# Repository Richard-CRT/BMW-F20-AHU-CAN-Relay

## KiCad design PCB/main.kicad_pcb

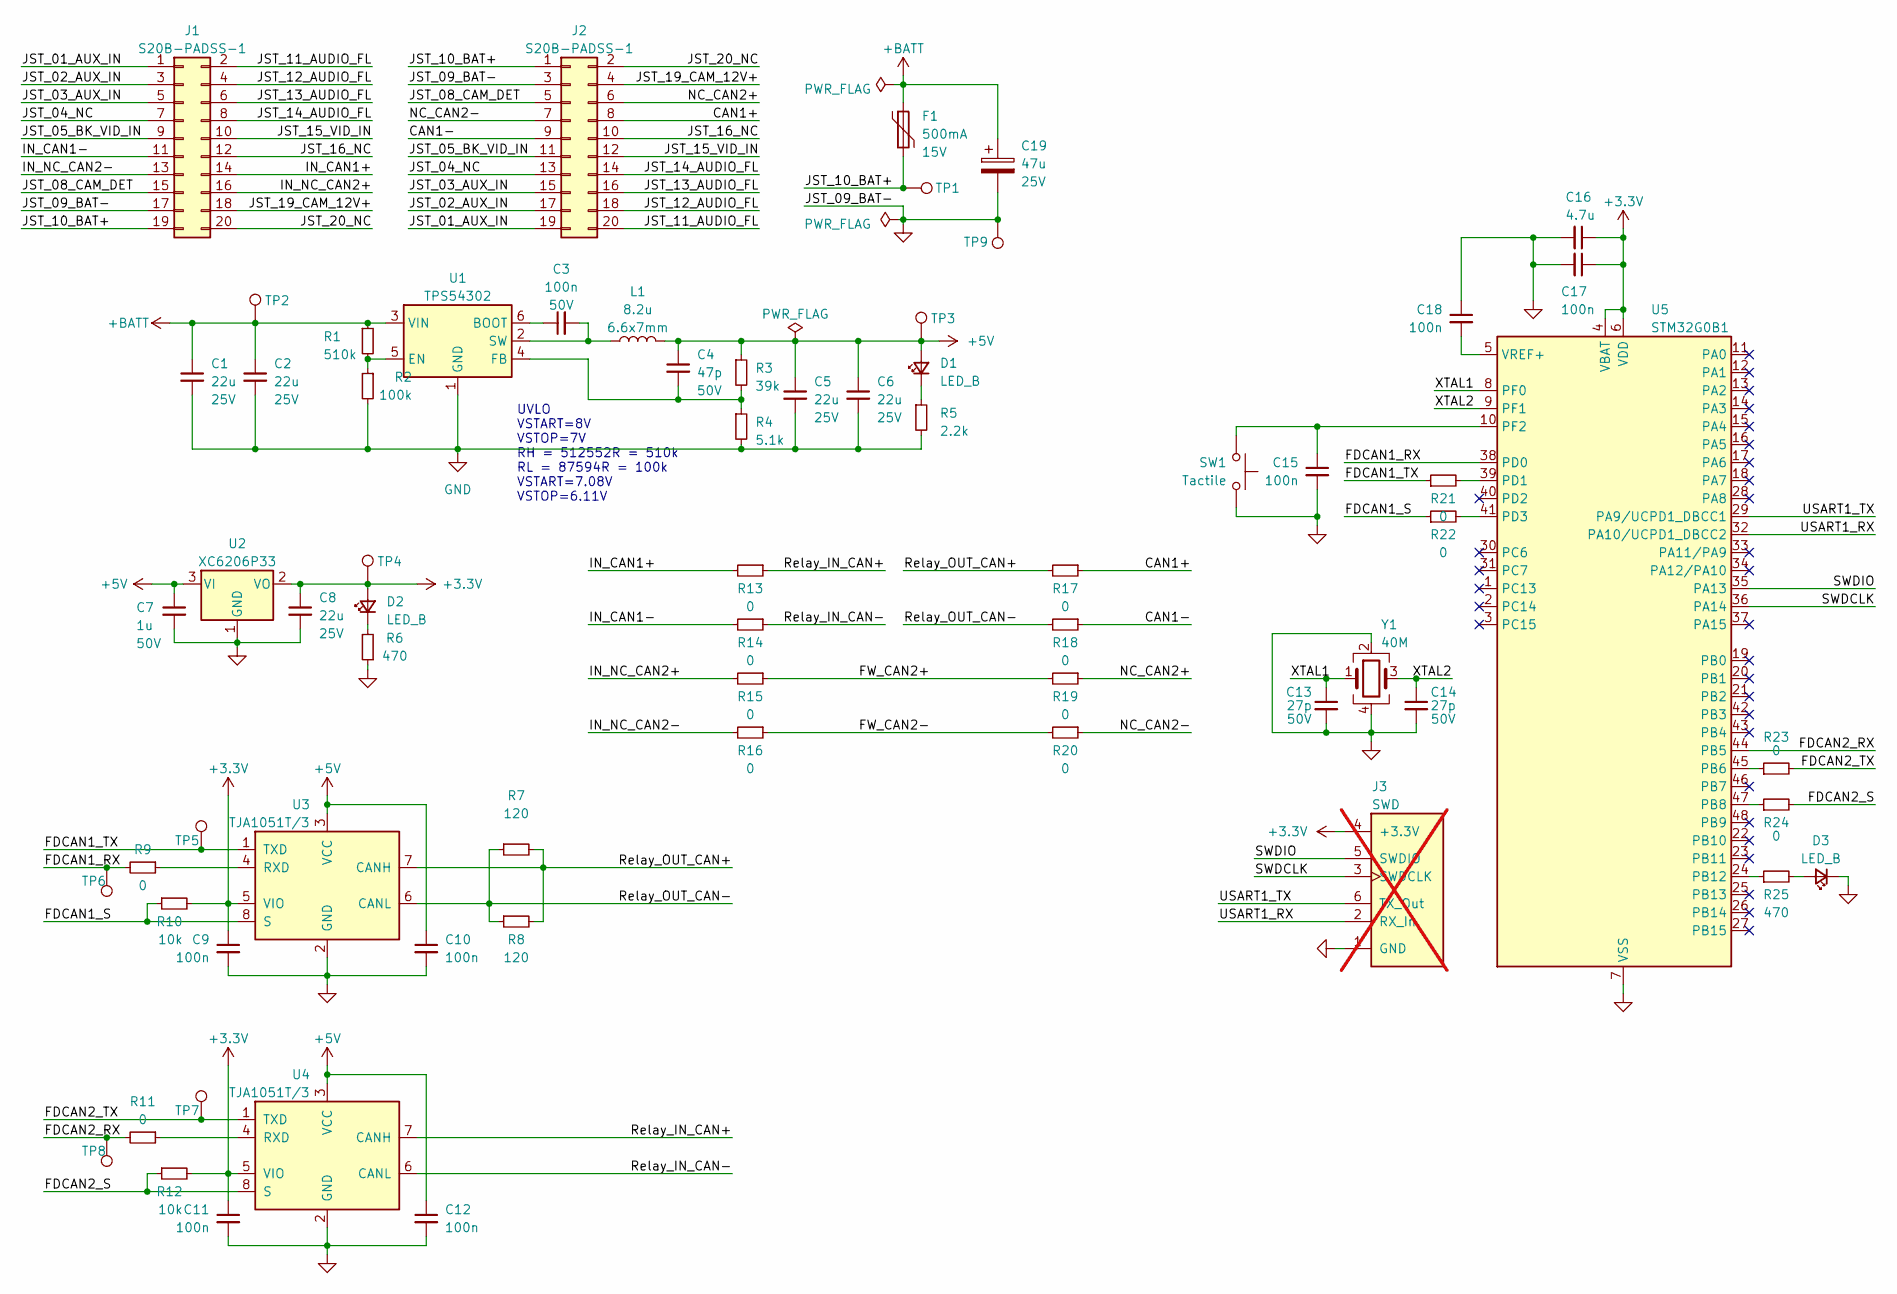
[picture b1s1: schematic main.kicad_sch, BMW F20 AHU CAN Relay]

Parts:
C1, C2, C5, C6, C8: 22u; C_1206_3216Metric; Capacitance Tolerance 10%; Voltage Rating 25V; MPN CL31A226KAHNNNE; LCSC C12891
C3, C9, C10, C11, C12, C15, C17, C18: 100n; C_0402_1005Metric; Capacitance Tolerance 10%; Voltage Rating 50V; MPN CL05B104KB54PNC; LCSC C307331
C4: 47p; C_0402_1005Metric; Capacitance Tolerance 5%; Voltage Rating 50V; MPN 0402CG470J500NT; LCSC C1567
C7: 1u; C_0805_2012Metric; Capacitance Tolerance 10%; Voltage Rating 50V; MPN CL21B105KBFNNNE; LCSC C28323
C13, C14: 27p; C_0402_1005Metric; Capacitance Tolerance 5%; Voltage Rating 50V; MPN 0402CG270J500NT; LCSC C1557
C16: 4.7u; C_0603_1608Metric; Capacitance Tolerance 10%; Voltage Rating 16V; MPN CL10A475KO8NNNC; LCSC C19666
C19: 47u; CP_Elec_6.3x5.8; Capacitance Tolerance 20%; Voltage Rating 25V; MPN EEE-FK1E470P; LCSC C178545
D1, D2, D3: LED_B; LED_0603_1608Metric; Forward Voltage 2.8V; MPN 19-217/BHC-ZL1M2RY/3T; LCSC C72041
F1: 500mA; CMP-0076; Max Voltage 15V; MPN 1812L050PR; LCSC C151169
J1, J2: S20B-PADSS-1; CMP-0012; MPN S20B-PADSS-1
J3: SWD; CMP-0053; not fitted
L1: 8.2u; CMP-0058; Inductance Tolerance 20%; MPN FXL0630-8R2-M; LCSC C167222
R1: 510k; R_0402_1005Metric; Tolerance 1%; Power Rating 62.5mW; MPN 0402WGF5103TCE; LCSC C11616
R2: 100k; R_0402_1005Metric; Tolerance 1%; Power Rating 62.5mW; MPN 0402WGF1003TCE; LCSC C25741
R3: 39k; R_0402_1005Metric; Tolerance 1%; Power Rating 62.5mW; MPN 0402WGF3902TCE; LCSC C25783
R4: 5.1k; R_0402_1005Metric; Tolerance 1%; Power Rating 62.5mW; MPN 0402WGF5101TCE; LCSC C25905
R5: 2.2k; R_0402_1005Metric; Tolerance 1%; Power Rating 62.5mW; MPN 0402WGF2201TCE; LCSC C25879
R6, R25: 470; R_0402_1005Metric; Tolerance 1%; Power Rating 62.5mW; MPN 0402WGF4700TCE; LCSC C25117
R7, R8: 120; R_1206_3216Metric; Tolerance 1%; Power Rating 250mW; MPN RC1206FR-07120RL; LCSC C114928
R9, R11, R13, R14, R15, R16, R17, R18, R19, R20, R21, R22, R23, R24: 0; R_0402_1005Metric; Tolerance 1%; Power Rating 62.5mW; MPN 0402WGF0000TCE; LCSC C17168
R10, R12: 10k; R_0402_1005Metric; Tolerance 1%; Power Rating 62.5mW; MPN 0402WGF1002TCE; LCSC C25744
SW1: Tactile; CMP-0072; MPN PTS810SJK250SMTRLFS; LCSC C221896
TP1, TP2, TP3, TP4, TP5, TP6, TP7, TP8, TP9: TestPoint; TestPoint_Pad_D1.0mm
U1: TPS54302; SOT-23-6; MPN TPS54302DDCR; LCSC C311983
U2: XC6206P33; CMP-0019; MPN XC6206P332MR-G; LCSC C5446
U3, U4: TJA1051T/3; SOIC-8_3.9x4.9mm_P1.27mm; MPN TJA1051T/3/1J; LCSC C38695
U5: STM32G0B1; LQFP-48_7x7mm_P0.5mm; MPN STM32G0B1CBT6; LCSC C2847904
Y1: 40M; Crystal_SMD_3225-4Pin_3.2x2.5mm; Tolerance 15 PPM; MPN X322540MPB4SI; LCSC C9010

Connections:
+3.3V: C8.1, C9.1, C11.1, C16.1, C17.1, D2.2 (A), J3.4 (+3.3V), R10.2, R12.2, TP4.1, U2.2 (VO), U3.5 (VIO), U4.5 (VIO), U5.4 (VBAT), U5.6 (VDD)
+5V: C4.1, C5.1, C6.1, C7.1, C10.1, C12.1, D1.2 (A), L1.2, R3.1, TP3.1, U2.3 (VI), U3.3 (VCC), U4.3 (VCC)
+BATT: C1.1, C2.1, C19.1, F1.1, R1.1, TP2.1, U1.3 (VIN)
/CAN1+: J2.8, R17.1
/CAN1-: J2.9, R18.1
/FDCAN1_RX: R9.2, TP6.1, U5.38 (PD0)
/FDCAN1_S: R10.1, R22.1, U3.8 (S)
/FDCAN1_TX: R21.1, TP5.1, U3.1 (TXD)
/FDCAN2_RX: R11.2, TP8.1, U5.44 (PB5)
/FDCAN2_S: R12.1, R24.2, U4.8 (S)
/FDCAN2_TX: R23.2, TP7.1, U4.1 (TXD)
/FW_CAN2+: R15.1, R19.2
/FW_CAN2-: R16.1, R20.2
/IN_CAN1+: J1.14, R13.2
/IN_CAN1-: J1.11, R14.2
/IN_NC_CAN2+: J1.16, R15.2
/IN_NC_CAN2-: J1.13, R16.2
/JST_01_AUX_IN: J1.1, J2.19
/JST_02_AUX_IN: J1.3, J2.17
/JST_03_AUX_IN: J1.5, J2.15
/JST_04_NC: J1.7, J2.13
/JST_05_BK_VID_IN: J1.9, J2.11
/JST_08_CAM_DET: J1.15, J2.5
/JST_10_BAT+: F1.2, J1.19, J2.1, TP1.1
/JST_11_AUDIO_FL: J1.2, J2.20
/JST_12_AUDIO_FL: J1.4, J2.18
/JST_13_AUDIO_FL: J1.6, J2.16
/JST_14_AUDIO_FL: J1.8, J2.14
/JST_15_VID_IN: J1.10, J2.12
/JST_16_NC: J1.12, J2.10
/JST_19_CAM_12V+: J1.18, J2.4
/JST_20_NC: J1.20, J2.2
/NC_CAN2+: J2.6, R19.1
/NC_CAN2-: J2.7, R20.1
/Relay_IN_CAN+: R13.1, U4.7 (CANH)
/Relay_IN_CAN-: R14.1, U4.6 (CANL)
/Relay_OUT_CAN+: R7.2, R8.2, R17.2, U3.7 (CANH)
/Relay_OUT_CAN-: R7.1, R8.1, R18.2, U3.6 (CANL)
/SWDCLK: J3.3 (SWDCLK), U5.36 (PA14)
/SWDIO: J3.5 (SWDIO), U5.35 (PA13)
/USART1_RX: J3.2 (RX_In), U5.32 (PA10/UCPD1_DBCC2)
/USART1_TX: J3.6 (TX_Out), U5.29 (PA9/UCPD1_DBCC1)
/XTAL1: C13.1, U5.8 (PF0), Y1.1
/XTAL2: C14.1, U5.9 (PF1), Y1.3
unnamed: D1.1 (K), R5.1
unnamed: D2.1 (K), R6.2
unnamed: D3.2 (A), R25.2
unnamed: C3.1, U1.6 (BOOT)
unnamed: R1.2, R2.1, U1.5 (EN)
unnamed: C4.2, R3.2, R4.1, U1.4 (FB)
unnamed: C3.2, L1.1, U1.2 (SW)
unnamed: R9.1, U3.4 (RXD)
unnamed: R11.1, U4.4 (RXD)
unnamed: R23.1, U5.45 (PB6)
unnamed: R24.1, U5.47 (PB8)
unnamed: R25.1, U5.24 (PB12)
unnamed: R21.2, U5.39 (PD1)
unnamed: R22.2, U5.41 (PD3)
unnamed: C15.1, SW1.1, U5.10 (PF2)
unnamed: C18.2, U5.5 (VREF+)

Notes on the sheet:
UVLO VSTART=8V VSTOP=7V RH = 512552R = 510k RL = 87594R = 100k VSTART=7.08V VSTOP=6.11V

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
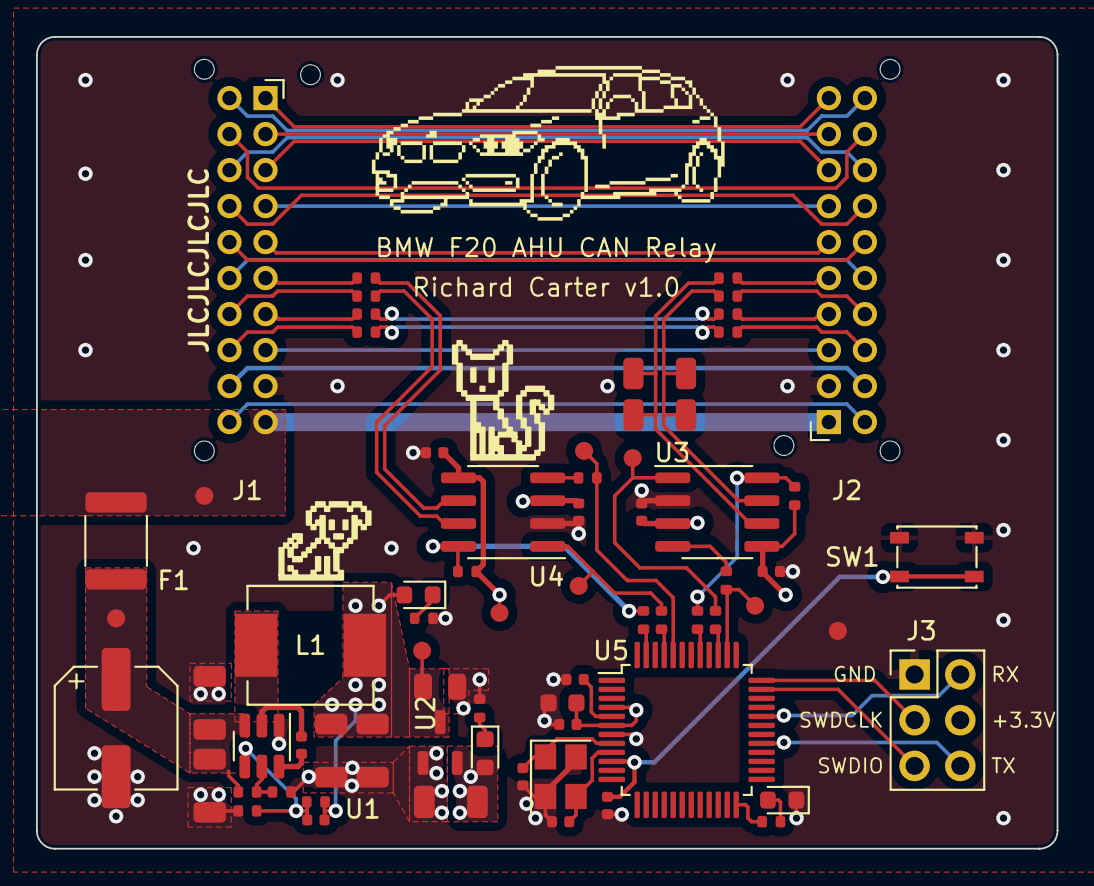
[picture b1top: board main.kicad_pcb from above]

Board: 4 copper layers, 56.7 x 45.1 mm, 69 parts (0 on the bottom side), 61 nets.

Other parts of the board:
ART3: JLCJLCJLCJLC; CMP-0047

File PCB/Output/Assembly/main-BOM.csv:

Comment,Designator,Footprint,LCSC Part #
22u CAP CER 22uF 25V X5R 1206,"C1,C2,C5,C6,C8",C_1206_3216Metric,C12891
100n CAP CER 100nF 50V X7R 0402,"C3,C9,C10,C11,C12,C15,C17,C18",C_0402_1005Metric,C307331
47p CAP CER 47pF 50V C0G 0402,C4,C_0402_1005Metric,C1567
1u CAP CER 1uF 50V X7R 0805,C7,C_0805_2012Metric,C28323
27p CAP CER 27pF 50V C0G 0402,"C13,C14",C_0402_1005Metric,C1557
4.7u CAP CER 4.7uF 16V X5R 0603,C16,C_0603_1608Metric,C19666
LED_B Blue LED Indication - Discrete 2.8V 0603 (1608 Metric),"D1,D2,D3",LED_0603_1608Metric,C72041
500mA 15V 500mA 100A -40℃~+85℃ 1A 150mΩ 150ms 1Ω 1812,F1,CMP-0076,C151169
"8.2u 5A 8.2uH ±20% 54mΩ 6A SMD,6.6x7mm Power Inductors",L1,CMP-0058,C167222
510k RES TF SMD 510k 1% 62.5mW 0402,R1,R_0402_1005Metric,C11616
100k RES TF SMD 100k 1% 62.5mW 0402,R2,R_0402_1005Metric,C25741
39k RES TF SMD 39k 1% 62.5mW 0402,R3,R_0402_1005Metric,C25783
5.1k RES TF SMD 5.1k 1% 62.5mW 0402,R4,R_0402_1005Metric,C25905
470 RES TF SMD 470 1% 62.5mW 0402,R5,R_0402_1005Metric,C25117
100 RES TF SMD 100 1% 62.5mW 0402,"R6,R25",R_0402_1005Metric,C25076
120 RES TF SMD 120R 1% 250mW 1206,"R7,R8",R_1206_3216Metric,C114928
0 RES TF SMD 0R 1% 62.5mW 0402,"R9,R11,R13,R14,R15,R16,R17,R18,R19,R20,R21,R22,R23,R24",R_0402_1005Metric,C17168
10k RES TF SMD 10k 1% 62.5mW 0402,"R10,R12",R_0402_1005Metric,C25744
TPS54302 Switching Voltage Regulators 5 to 28V Input 3A Step Down Converter ,U1,SOT-23-6,C311983
"XC6206P33 LDO Voltage Regulators 1uA Low Quiescent 3 Terminal, Low ESR Cap. Compatible, Voltage Regulator ",U2,CMP-0019,C5446
TJA1051T/3 CAN Interface IC High-speed CAN transceiver ,"U3,U4",SOIC-8_3.9x4.9mm_P1.27mm,C38695
STM32G0B1 ARM Microcontrollers - MCU Mainstream Arm Cortex-M0+ 32-bit MCU up to 128KB Flash 144KB RAM,U5,LQFP-48_7x7mm_P0.5mm,C2847904
40M Crystal 40MHz 15pF SMD ,Y1,Crystal_SMD_3225-4Pin_3.2x2.5mm,C9010

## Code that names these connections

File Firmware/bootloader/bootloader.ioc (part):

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Mcu.Name=STM32G0B1C(B-C-E)Tx
Mcu.Package=LQFP48
Mcu.UserName=STM32G0B1CBTx
PA10.Mode=Asynchronous
PA10.Signal=USART1_RX
PA13.Mode=Serial_Wire
PA13.Signal=SYS_SWDIO
PA14-BOOT0.Mode=Serial_Wire
PA14-BOOT0.Signal=SYS_SWCLK
PA9.Mode=Asynchronous
PA9.Signal=USART1_TX
PB12.GPIOParameters=GPIO_Label
PB12.GPIO_Label=LED
PB12.Signal=GPIO_Output
PB5.GPIOParameters=GPIO_PuPd
PB5.GPIO_PuPd=GPIO_PULLUP
PB5.Mode=FDCAN_Activate
PB5.Signal=FDCAN2_RX
PB6.Mode=FDCAN_Activate
PB6.Signal=FDCAN2_TX
PB8.GPIOParameters=GPIO_Label
PB8.GPIO_Label=FDCAN2_S
PB8.Signal=GPIO_Output
PD0.GPIOParameters=GPIO_PuPd
PD0.GPIO_PuPd=GPIO_PULLUP
PD0.Mode=FDCAN_Activate
PD0.Signal=FDCAN1_RX
PD1.Mode=FDCAN_Activate
PD1.Signal=FDCAN1_TX
PD3.GPIOParameters=GPIO_Label
PD3.GPIO_Label=FDCAN1_S
PD3.Signal=GPIO_Output
PF0-OSC_IN\ (PF0).Mode=HSE-External-Oscillator
PF0-OSC_IN\ (PF0).Signal=RCC_OSC_IN
PF1-OSC_OUT\ (PF1).Mode=HSE-External-Oscillator
PF1-OSC_OUT\ (PF1).Signal=RCC_OSC_OUT
RCC.HSE_VALUE=40000000
RCC.SYSCLKFreq_VALUE=16000000
board=custom

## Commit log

2023-03-01 Create PCB project
2023-03-01 Add gitignore
2023-03-01 General design
2023-03-04 Develop schematic a little and create initial software project
2023-03-04 Develop board
2023-03-04 Continue configuring IC
2023-03-05 Further develop board
2023-03-05 Finish schematic
2023-03-05 Add blinky LED
2023-03-05 Switch Silent mode on by default
2023-03-05 Disable pull-down on pins since want pull-up and external ones added
2023-03-06 Add fuse holder
2023-03-07 Change buck converter
2023-03-07 Continue development
2023-03-07 Add JLCJLCJLCJLC placeholder artwork
2023-03-08 Start layout, but intend to ditch the 0ohm resistors and be confident CAN1 is the right one (remember 0402 links)
2023-03-08 Start relayout
2023-03-08 Add UART and mostly complete layout
2023-03-09 Tweak proj settings
2023-03-10 Remove / from case/package
2023-03-11 Switch to multi library parts system
2023-03-11 Start moving to TPS54302
2023-03-11 Re-layout with TPS54302
2023-03-12 Start changing LDO
2023-03-12 Further development, started final GND pour
2023-03-12 Finish plane layout
2023-03-12 Generate gerbers
2023-03-12 Update gitignore
2023-03-12 Switch to TJA1051T/3
2023-03-13 Added bulk capacitance
2023-03-13 Generate output files
2023-03-13 Change switch
2023-03-13 Redo layout to support use of B20B-PADSS due to stock inavailability
2023-03-13 Add boss hole incase I need to use B20B-PADSS-1F
2023-03-14 Plot schematic
2023-03-14 Change fuse and adjust board size
2023-03-14 Update car graphic
2023-03-19 Start code project
2023-03-31 Change blinky length
2023-03-31 Improve thermal relief
2023-03-31 Start primary harness drawing
2023-04-01 Finish cable drawing pending length confirmation
2023-04-01 Fix typo for wire bom ID in elec wiring diagram
2023-04-01 Reduce LED brightness
2023-04-02 Continue development of firmware, interrupt UART setup
2023-04-02 Update lengths
2023-04-04 Update drawing with revised pin numbering scheme
2023-04-04 Make some improvements including bringing the lost test points back
2023-04-04 Change fuse model
2023-04-04 Adjust board colours and generate renders
2023-04-07 Significant work on CANBUS code
2023-04-08 Create necessary functions to forward messages
2023-04-09 Further dev
2023-04-09 Test in car and make necessary adjustments
2023-04-09 Add delayed shutdown
2023-04-09 Correct comment
2023-04-10 Further development to improve performance
2023-04-15 Switch to properly defined FSM
2023-04-15 Potentially fix turn off bug
2023-04-15 Remove old func prototype
2023-04-22 Fix period of timer
2023-04-23 Restructure significantly, attempt to fix bug by disabling auto error retransmission on AHU side, add bootloader that doesn't do anything yet
2023-04-25 Work on bootloader, potentially improve FIFO count (untested)
2023-05-10 Re-add necessary include
2023-05-10 Remove old include path that was throwing error
2023-05-10 Fix print lengths and comment unused code
